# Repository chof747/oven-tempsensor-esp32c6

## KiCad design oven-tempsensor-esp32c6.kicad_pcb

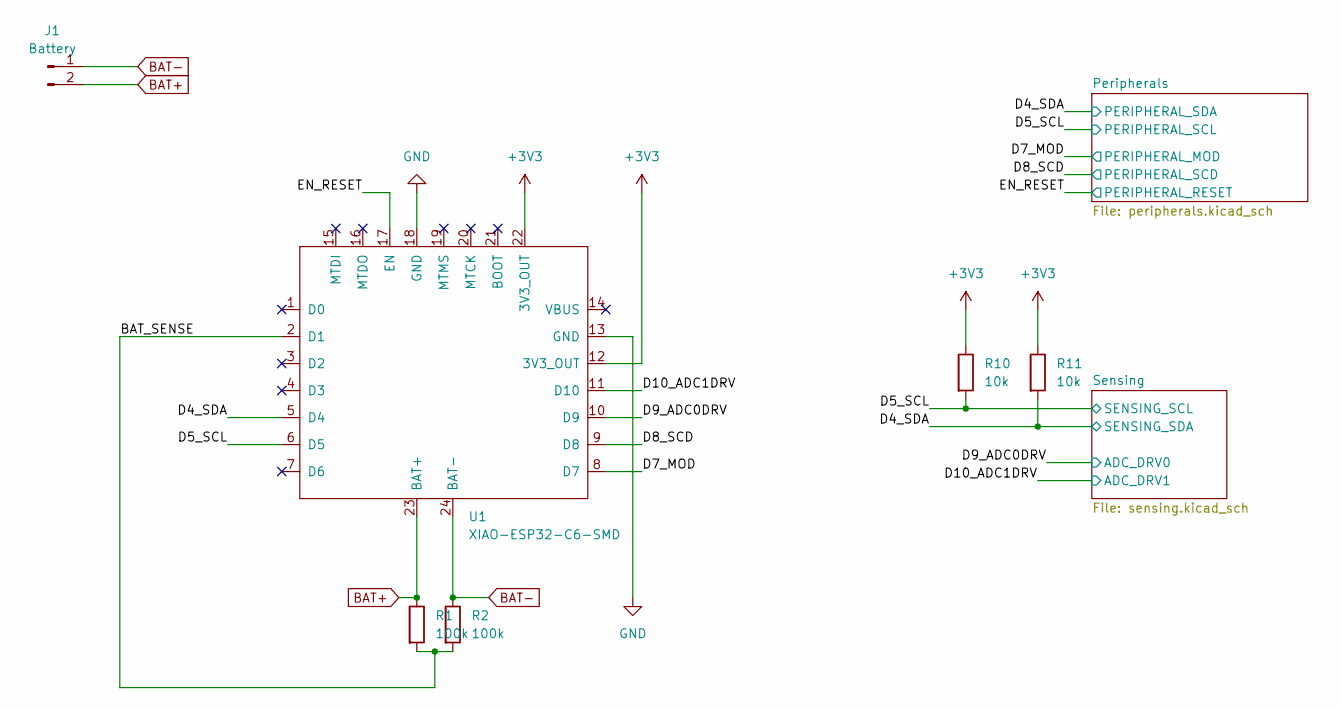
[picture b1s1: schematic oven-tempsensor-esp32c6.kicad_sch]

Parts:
J1: Battery; PinHeader_1x02_P2.54mm_Horizontal
R1, R2: 100k; R_0603_1608Metric_Pad0.98x0.95mm_HandSolder
R10, R11: 10k; R_0603_1608Metric_Pad0.98x0.95mm_HandSolder
U1: XIAO-ESP32-C6-SMD; XIAO-ESP32-C6-DIP

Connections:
+3V3: R10.1, R11.1, U1.12 (3V3_OUT), U1.22 (3V3_OUT); also elsewhere on the board
/BAT_SENSE: R1.2, R2.2, U1.2 (D1)
/D4_SDA: R11.2, U1.5 (D4); also elsewhere on the board
/D5_SCL: R10.2, U1.6 (D5); also elsewhere on the board
/D7_MOD: U1.8 (D7); also elsewhere on the board
/D8_SCD: U1.9 (D8); also elsewhere on the board
/D9_ADC0DRV: U1.10 (D9); also elsewhere on the board
/D10_ADC1DRV: U1.11 (D10); also elsewhere on the board
/EN_RESET: U1.17 (EN); also elsewhere on the board
BAT+: J1.2, R1.1, U1.23 (BAT+)
BAT-: J1.1, R2.1, U1.24 (BAT-)
GND: U1.13 (GND), U1.18 (GND); also elsewhere on the board

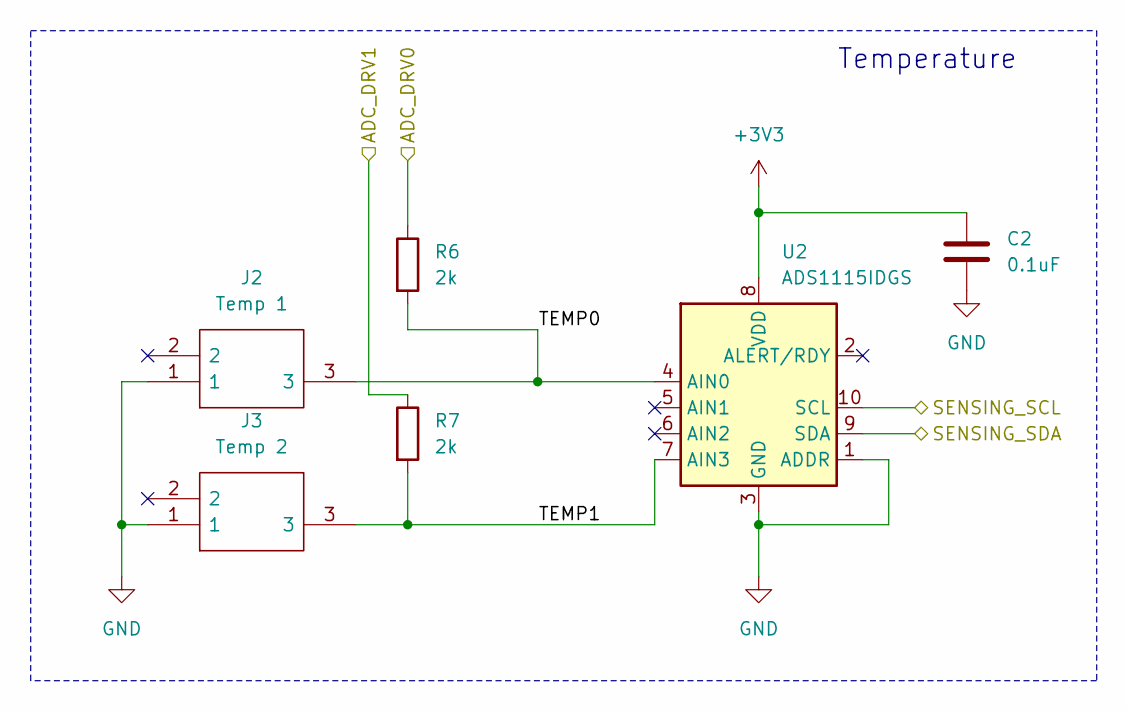
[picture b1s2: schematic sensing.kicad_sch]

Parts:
C2: 0.1uF; C_0603_1608Metric_Pad1.08x0.95mm_HandSolder
J2: Temp 1; MJ2509N; Manufacturer_Part_Number MJ-2509N; Mouser Part Number 490-MJ-2509N
J3: Temp 2; MJ2509N; Manufacturer_Part_Number MJ-2509N; Mouser Part Number 490-MJ-2509N
R6, R7: 2k; R_0603_1608Metric_Pad0.98x0.95mm_HandSolder
U2: ADS1115IDGS; TSSOP-10_3x3mm_P0.5mm

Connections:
+3V3: C2.1, U2.8 (VDD); also elsewhere on the board
/D4_SDA: U2.9 (SDA); also elsewhere on the board
/D5_SCL: U2.10 (SCL); also elsewhere on the board
/D9_ADC0DRV: R6.1; also elsewhere on the board
/D10_ADC1DRV: R7.1; also elsewhere on the board
/Sensing/TEMP0: J2.3, R6.2, U2.4 (AIN0)
/Sensing/TEMP1: J3.3, R7.2, U2.7 (AIN3)
GND: C2.2, J2.1, J3.1, U2.1 (ADDR), U2.3 (GND); also elsewhere on the board

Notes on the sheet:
Temperature

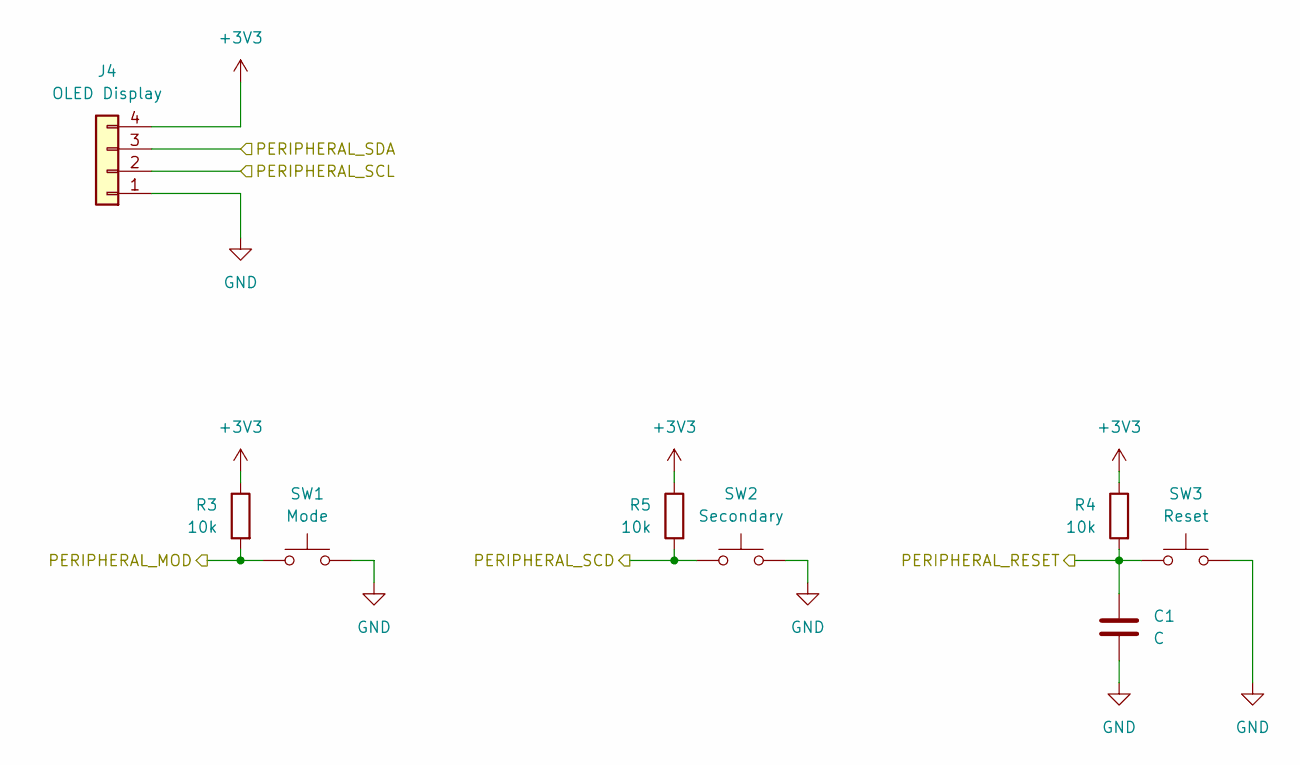
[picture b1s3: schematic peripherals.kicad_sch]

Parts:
C1: C; C_0603_1608Metric_Pad1.08x0.95mm_HandSolder
J4: OLED Display; OLED-TH_L38.0-W12.0_HS91L02W2C01
R3, R4, R5: 10k; R_0603_1608Metric_Pad0.98x0.95mm_HandSolder
SW1: Mode; SW_PUSH_6mm
SW2: Secondary; SW_PUSH_6mm
SW3: Reset; SW_PUSH_6mm

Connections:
+3V3: J4.4, R3.1, R4.1, R5.1; also elsewhere on the board
/D4_SDA: J4.3; also elsewhere on the board
/D5_SCL: J4.2; also elsewhere on the board
/D7_MOD: R3.2, SW1.1; also elsewhere on the board
/D8_SCD: R5.2, SW2.1; also elsewhere on the board
/EN_RESET: C1.1, R4.2, SW3.1; also elsewhere on the board
GND: C1.2, J4.1, SW1.2, SW2.2, SW3.2; also elsewhere on the board

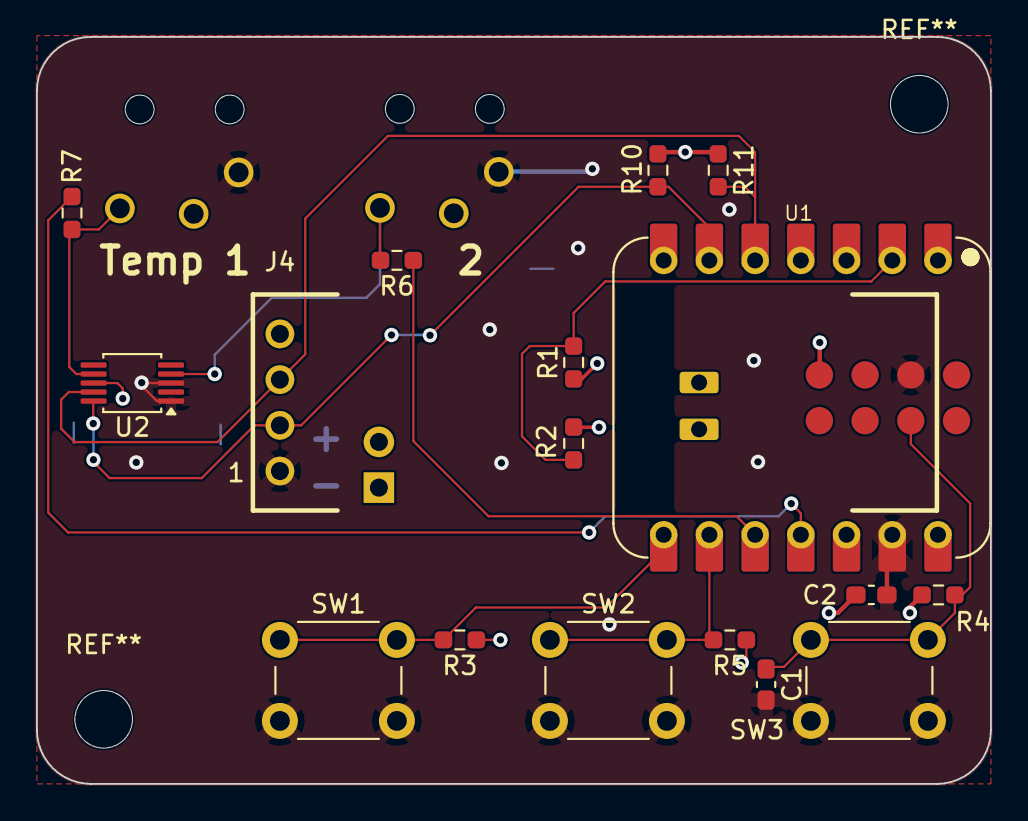
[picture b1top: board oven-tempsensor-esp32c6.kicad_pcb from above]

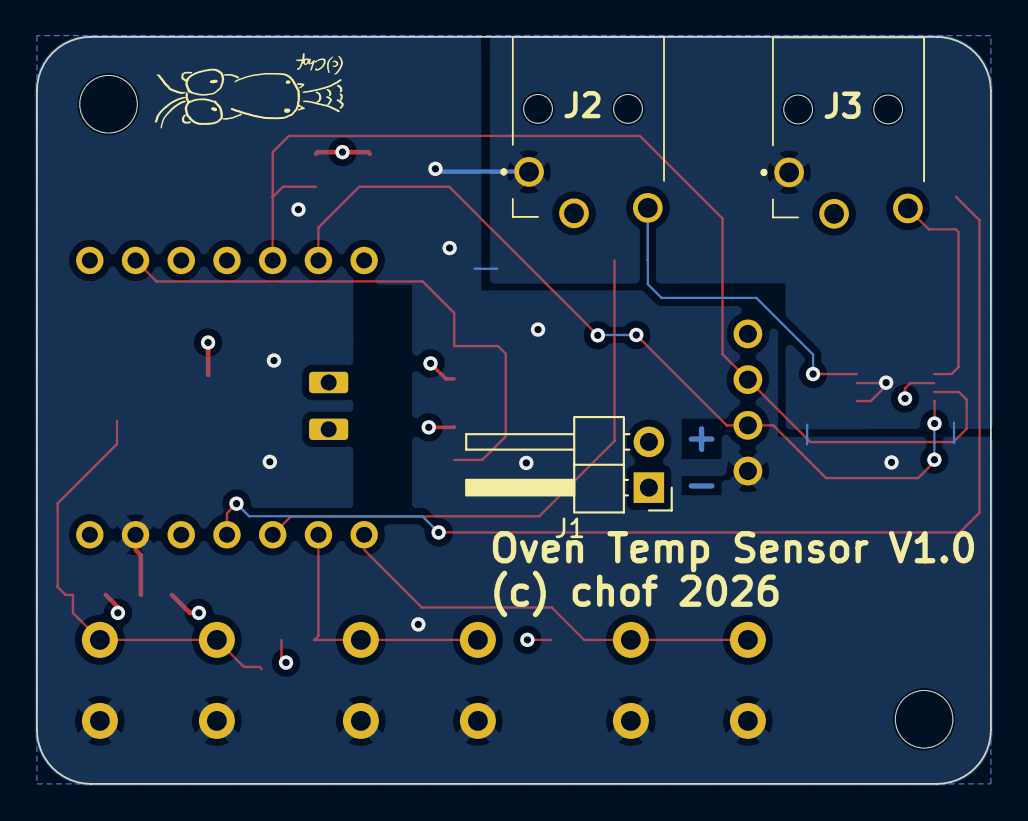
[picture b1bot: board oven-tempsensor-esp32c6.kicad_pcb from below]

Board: 4 copper layers, 53.0 x 41.5 mm, 20 parts (3 on the bottom side), 14 nets.
